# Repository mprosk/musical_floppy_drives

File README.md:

# Musical Floppy Drives

Repo containing a number of project files relating to a setup of musical floppy drives

## floppy_dds

Firmware for the Arduino Mega allowing control of up to 16 floppy drives. Accepts MIDI in. Any notes that cannot be allocated to a free drive will be forwarded out the MIDI OUT, allowing multiple Megas to be cascaded to control more than 16 drives with no code changes. Tone generation is performed using direct digital synthesis (DDS). Intended to be used with the `floppy_mega` breakout board.

## floppy_mega

Shield for the Arduino Mega that exposes 16 headers for connecting floppy drives. Intended to be paired with the `floppy_dds` firmware.

## floppy_bracket

PCB bracket designed to bind four floppy drives together. Two PCBs should be used.

## floppy_power

Power bus board

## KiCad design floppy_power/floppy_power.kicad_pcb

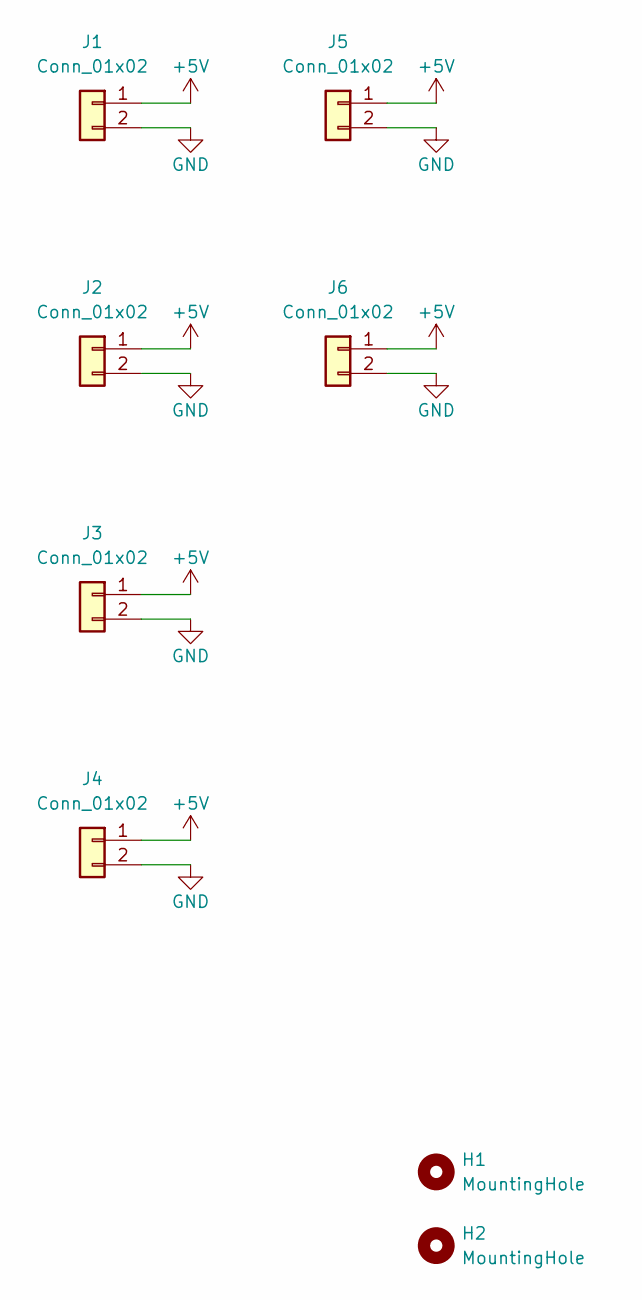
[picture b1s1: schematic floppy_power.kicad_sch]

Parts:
H1, H2: MountingHole; MountingHole_3.2mm_M3
J1, J2, J3, J4, J5, J6: Conn_01x02; TerminalBlock_Phoenix_MPT-0,5-2-2.54_1x02_P2.54mm_Horizontal

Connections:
+5V: J1.1, J2.1, J3.1, J4.1, J5.1, J6.1
GND: J1.2, J2.2, J3.2, J4.2, J5.2, J6.2

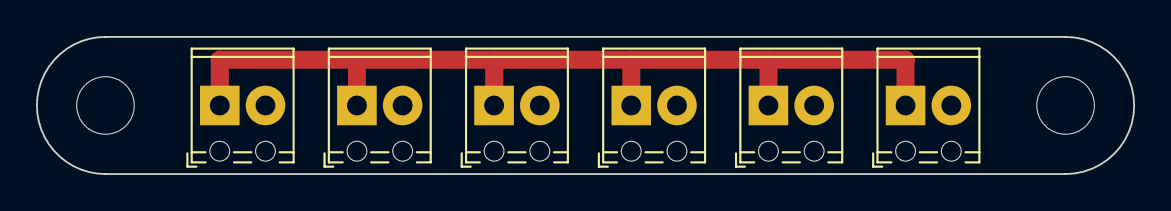
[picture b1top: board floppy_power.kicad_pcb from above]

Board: 2 copper layers, 61.0 x 7.6 mm, 8 parts (0 on the bottom side), 2 nets.

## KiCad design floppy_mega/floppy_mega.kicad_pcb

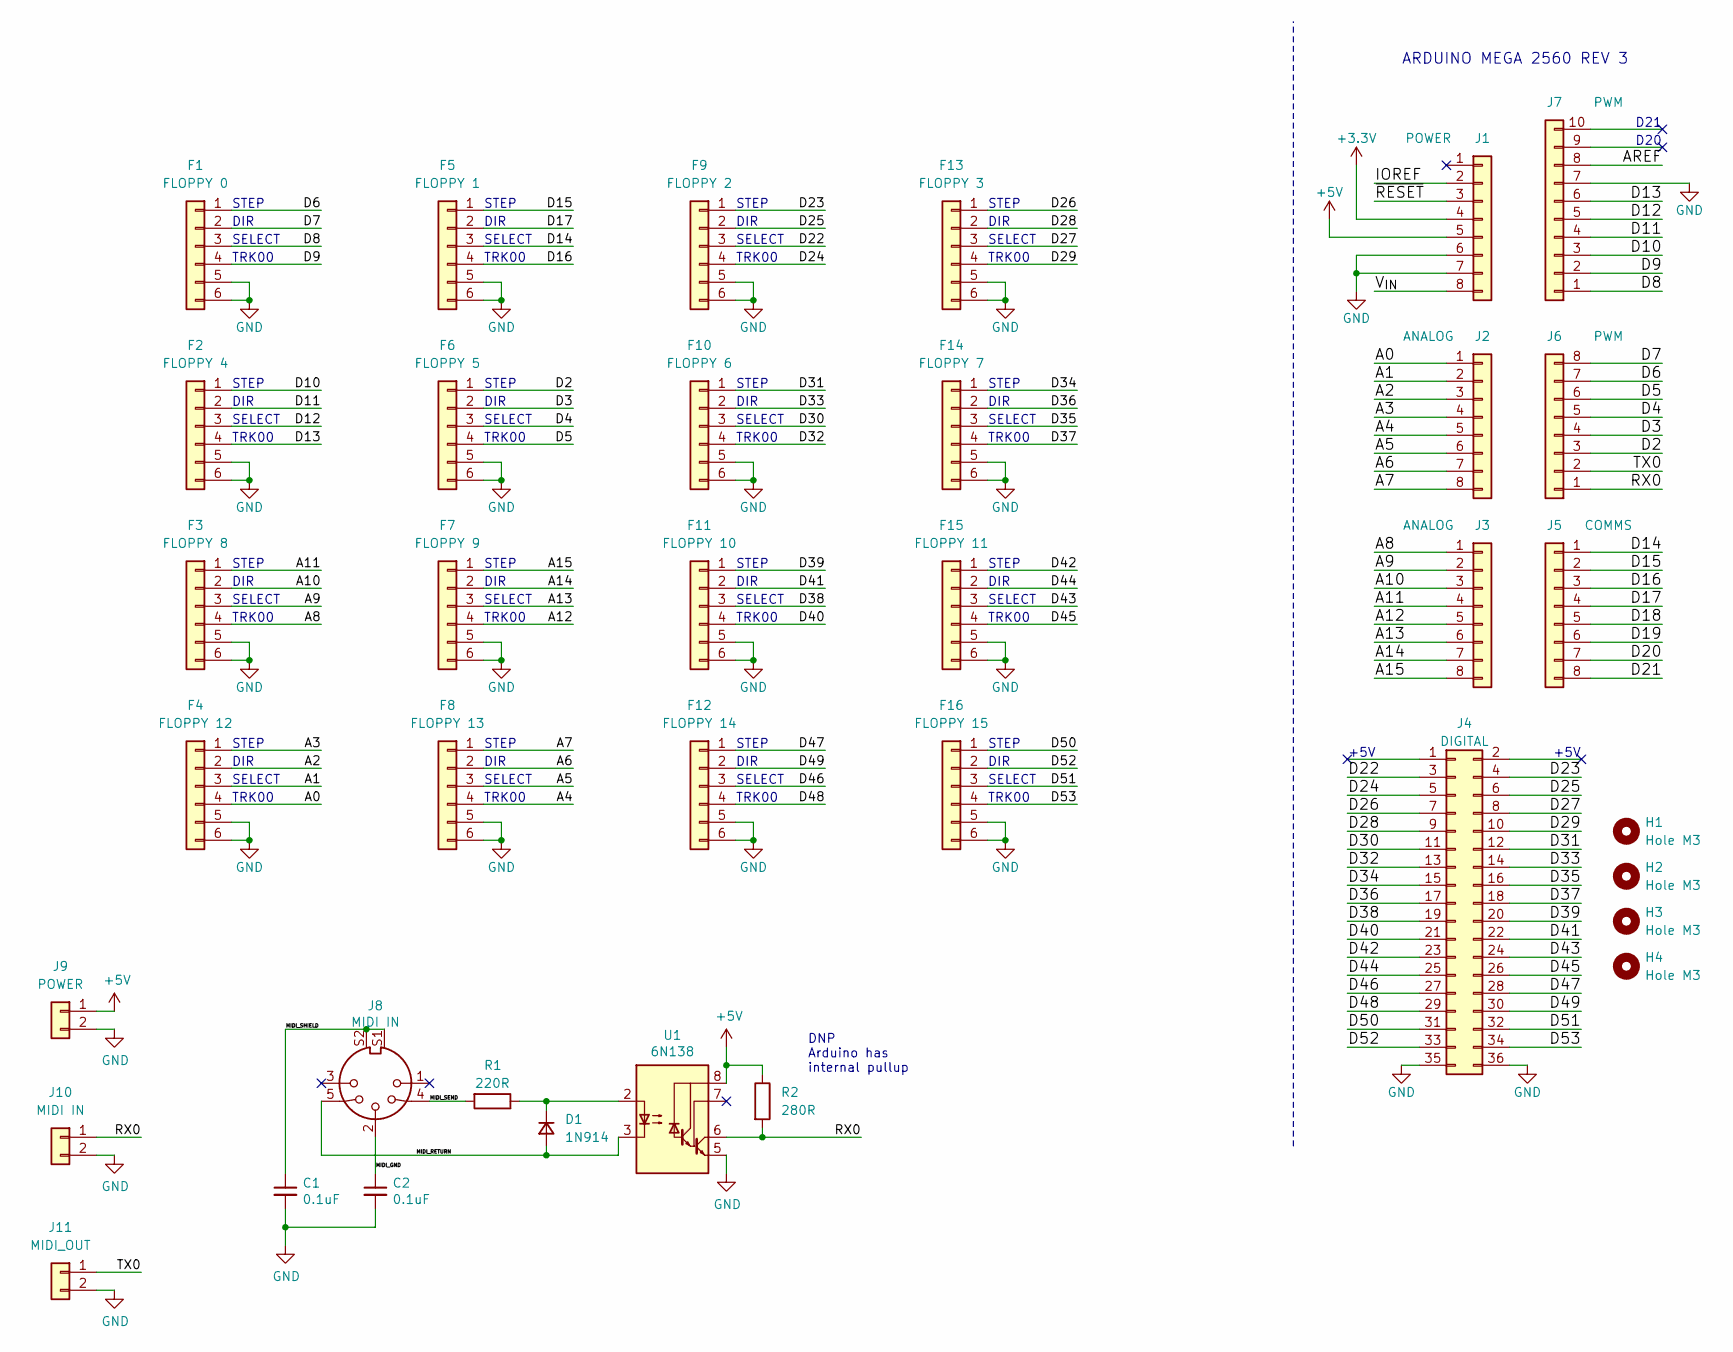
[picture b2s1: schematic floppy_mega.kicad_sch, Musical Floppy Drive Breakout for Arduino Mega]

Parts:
C1, C2: 0.1uF; C_Disc_D3.0mm_W1.6mm_P2.50mm
D1: 1N914; D_DO-34_SOD68_P7.62mm_Horizontal
F1: FLOPPY 0; PinHeader_2x03_P2.54mm_Vertical
F2: FLOPPY 4; PinHeader_2x03_P2.54mm_Vertical
F3: FLOPPY 8; PinHeader_2x03_P2.54mm_Vertical
F4: FLOPPY 12; PinHeader_2x03_P2.54mm_Vertical
F5: FLOPPY 1; PinHeader_2x03_P2.54mm_Vertical
F6: FLOPPY 5; PinHeader_2x03_P2.54mm_Vertical
F7: FLOPPY 9; PinHeader_2x03_P2.54mm_Vertical
F8: FLOPPY 13; PinHeader_2x03_P2.54mm_Vertical
F9: FLOPPY 2; PinHeader_2x03_P2.54mm_Vertical
F10: FLOPPY 6; PinHeader_2x03_P2.54mm_Vertical
F11: FLOPPY 10; PinHeader_2x03_P2.54mm_Vertical
F12: FLOPPY 14; PinHeader_2x03_P2.54mm_Vertical
F13: FLOPPY 3; PinHeader_2x03_P2.54mm_Vertical
F14: FLOPPY 7; PinHeader_2x03_P2.54mm_Vertical
F15: FLOPPY 11; PinHeader_2x03_P2.54mm_Vertical
F16: FLOPPY 15; PinHeader_2x03_P2.54mm_Vertical
H1, H2, H3, H4: Hole M3; MountingHole_3.2mm_M3
J1: POWER; PinHeader_1x08_P2.54mm_Vertical
J2, J3: ANALOG; PinHeader_1x08_P2.54mm_Vertical
J4: DIGITAL; PinHeader_2x18_P2.54mm_Vertical
J5: COMMS; PinHeader_1x08_P2.54mm_Vertical
J6: PWM; PinHeader_1x08_P2.54mm_Vertical
J7: PWM; PinHeader_1x10_P2.54mm_Vertical
J8: MIDI IN; CUI_SDS-50J
J9: POWER; TerminalBlock_Phoenix_MPT-0,5-2-2.54_1x02_P2.54mm_Horizontal
J10: MIDI IN; PinHeader_1x02_P2.54mm_Vertical
J11: MIDI_OUT; PinHeader_1x02_P2.54mm_Vertical
R1: 220R; R_Axial_DIN0207_L6.3mm_D2.5mm_P10.16mm_Horizontal
R2: 280R; R_Axial_DIN0207_L6.3mm_D2.5mm_P10.16mm_Horizontal
U1: 6N138; DIP-8_W7.62mm

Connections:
+3V3: J1.4
+5V: J1.5, J9.1, R2.1, U1.8 (VCC)
/A0: F4.4, J2.1
/A1: F4.3, J2.2
/A2: F4.2, J2.3
/A3: F4.1, J2.4
/A4: F8.4, J2.5
/A5: F8.3, J2.6
/A6: F8.2, J2.7
/A7: F8.1, J2.8
/A8: F3.4, J3.1
/A9: F3.3, J3.2
/A10: F3.2, J3.3
/A11: F3.1, J3.4
/A12: F7.4, J3.5
/A13: F7.3, J3.6
/A14: F7.2, J3.7
/A15: F7.1, J3.8
/AREF: J7.8
/D2: F6.1, J6.3
/D3: F6.2, J6.4
/D4: F6.3, J6.5
/D5: F6.4, J6.6
/D6: F1.1, J6.7
/D7: F1.2, J6.8
/D8: F1.3, J7.1
/D9: F1.4, J7.2
/D10: F2.1, J7.3
/D11: F2.2, J7.4
/D12: F2.3, J7.5
/D13: F2.4, J7.6
/D14: F5.3, J5.1
/D15: F5.1, J5.2
/D16: F5.4, J5.3
/D17: F5.2, J5.4
/D18: J5.5
/D19: J5.6
/D20: J5.7
/D21: J5.8
/D22: F9.3, J4.3
/D23: F9.1, J4.4
/D24: F9.4, J4.5
/D25: F9.2, J4.6
/D26: F13.1, J4.7
/D27: F13.3, J4.8
/D28: F13.2, J4.9
/D29: F13.4, J4.10
/D30: F10.3, J4.11
/D31: F10.1, J4.12
/D32: F10.4, J4.13
/D33: F10.2, J4.14
/D34: F14.1, J4.15
/D35: F14.3, J4.16
/D36: F14.2, J4.17
/D37: F14.4, J4.18
/D38: F11.3, J4.19
/D39: F11.1, J4.20
/D40: F11.4, J4.21
/D41: F11.2, J4.22
/D42: F15.1, J4.23
/D43: F15.3, J4.24
/D44: F15.2, J4.25
/D45: F15.4, J4.26
/D46: F12.3, J4.27
/D47: F12.1, J4.28
/D48: F12.4, J4.29
/D49: F12.2, J4.30
/D50: F16.1, J4.31
/D51: F16.3, J4.32
/D52: F16.2, J4.33
/D53: F16.4, J4.34
/IOREF: J1.2
/MIDI_GND: C2.1, J8.2
/MIDI_RETURN: D1.2 (A), J8.5, U1.3 (C2)
/MIDI_SEND: J8.4, R1.2
/MIDI_SHIELD: C1.1, J8.S1, J8.S2
/RX0: J6.1, J10.1, R2.2, U1.6 (VO2)
/TX0: J6.2, J11.1
/V_{IN}: J1.8
/~RESET: J1.3
GND: C1.2, C2.2, F1.5, F1.6, F2.5, F2.6, F3.5, F3.6, F4.5, F4.6, F5.5, F5.6, F6.5, F6.6, F7.5, F7.6, F8.5, F8.6, F9.5, F9.6, F10.5, F10.6, F11.5, F11.6, F12.5, F12.6, F13.5, F13.6, F14.5, F14.6, F15.5, F15.6, F16.5, F16.6, J1.6, J1.7, J4.35, J4.36, J7.7, J9.2, J10.2, J11.2, U1.5 (GND)
unnamed: D1.1 (K), R1.1, U1.2 (C1)

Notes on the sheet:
TRK00
SELECT
STEP
DIR
+5V
DNP Arduino has internal pullup
D21
D20
ARDUINO MEGA 2560 REV 3

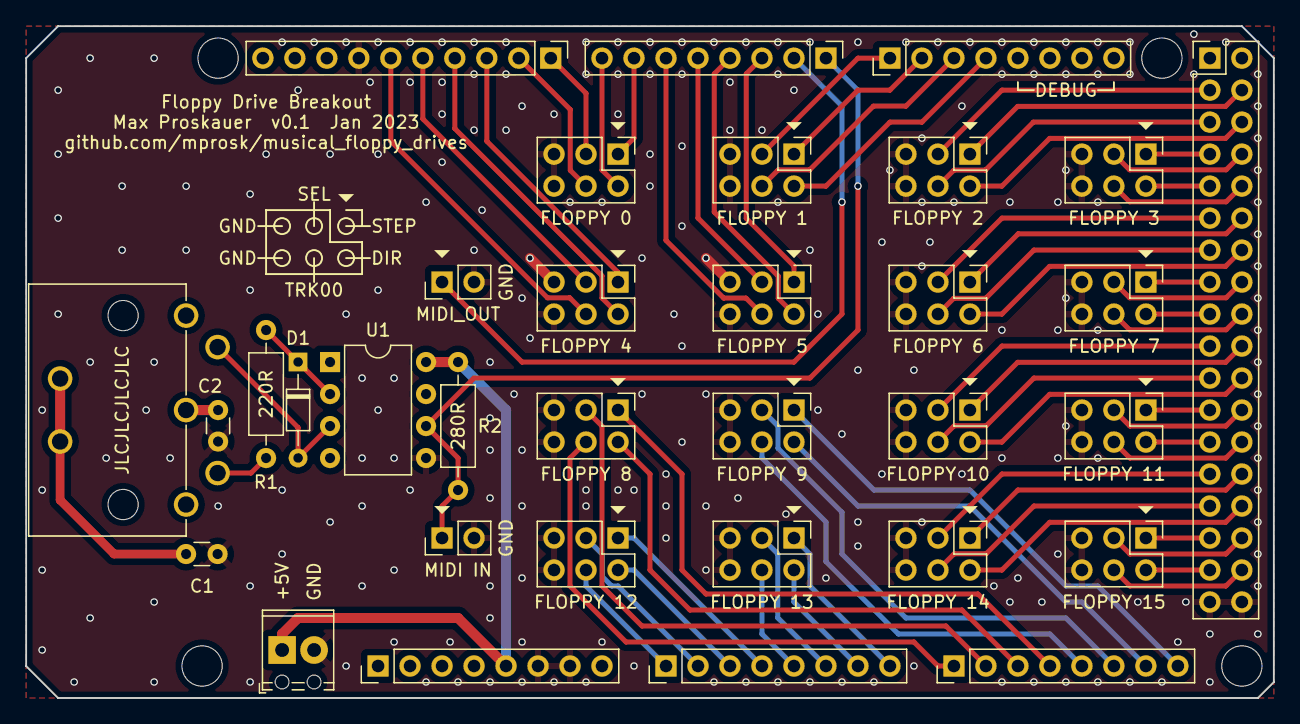
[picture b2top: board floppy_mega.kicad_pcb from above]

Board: 2 copper layers, 99.1 x 53.3 mm, 37 parts (0 on the bottom side), 73 nets.

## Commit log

2023-01-19 Add files from local repo
2023-01-19 Add project files for floppy drive bracket
2023-01-19 Add github link to breakout board
2023-01-19 Remove refernce designator from mounting holes
2023-02-22 Finalize bracket
2023-02-22 Add power distribution PCB
2023-02-22 Get software working. Fix bugs in midi.cpp
